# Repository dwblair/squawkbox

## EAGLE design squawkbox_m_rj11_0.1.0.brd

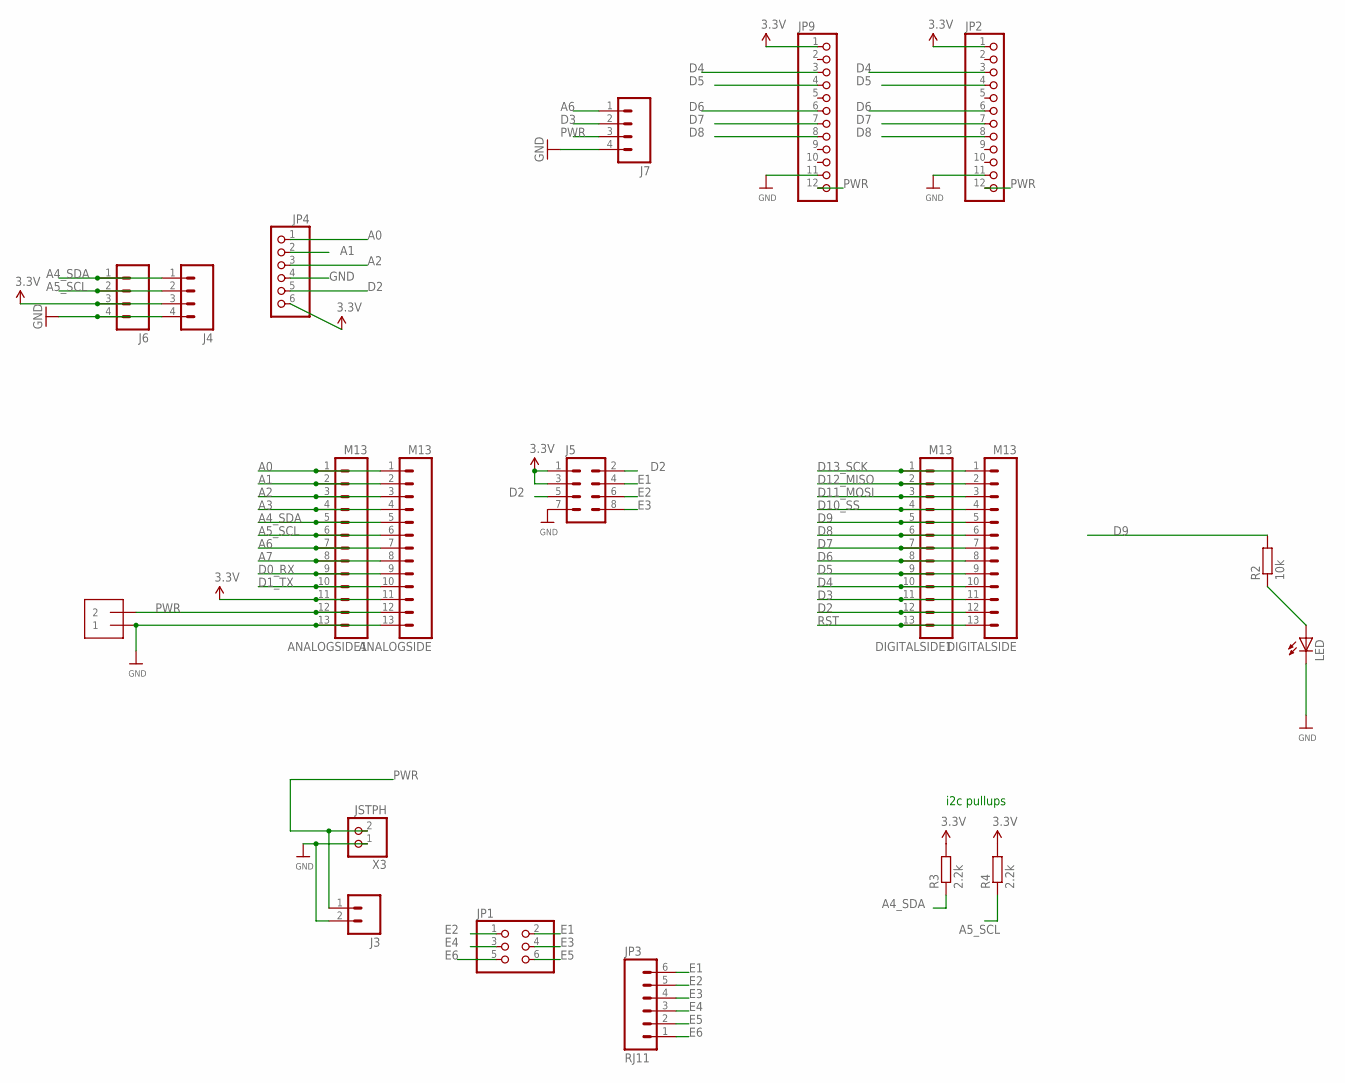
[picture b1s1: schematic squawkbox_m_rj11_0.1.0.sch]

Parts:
ANALOGSIDE, ANALOGSIDE1: M13; 1X13
DIGITALSIDE, DIGITALSIDE1: M13; 1X13
J2: 1X2-3.5MM
J3: M02PTH; 1X02
J4: M04PTH; 1X04
J5: M04X2; 2X4
J6, J7: M04SCREW; SCREWTERMINAL-3.5MM-4
JP1: PINHD-2X3; 2X03
JP2, JP9: PINHD-1X12-CB; 1X12-CB
JP3: RJ11; RJ11-6
JP4: PINHD-1X6-3.5MM; 1X06-3.5MM
LED: LED3MM
R2: 10k; 0204/7
R3, R4: 2.2k; 0204/7
X3: JSTPH; JSTPH2

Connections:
A0: ANALOGSIDE.1, ANALOGSIDE1.1, JP4.1
A1: ANALOGSIDE.2, ANALOGSIDE1.2, JP4.2
A2: ANALOGSIDE.3, ANALOGSIDE1.3, JP4.3
A3: ANALOGSIDE.4, ANALOGSIDE1.4
A4_SDA: ANALOGSIDE.5, ANALOGSIDE1.5, J4.1, J6.1, R3.1
A5_SCL: ANALOGSIDE.6, ANALOGSIDE1.6, J4.2, J6.2, R4.1
A6: ANALOGSIDE.7, ANALOGSIDE1.7, J7.1
A7: ANALOGSIDE.8, ANALOGSIDE1.8
D0_RX: ANALOGSIDE.9, ANALOGSIDE1.9
D1_TX: ANALOGSIDE.10, ANALOGSIDE1.10
D2: DIGITALSIDE.12, DIGITALSIDE1.12, J5.2, J5.5, JP4.5
D3: DIGITALSIDE.11, DIGITALSIDE1.11, J7.2
D4: DIGITALSIDE.10, DIGITALSIDE1.10, JP2.3, JP9.3
D5: DIGITALSIDE.9, DIGITALSIDE1.9, JP2.4, JP9.4
D6: DIGITALSIDE.8, DIGITALSIDE1.8, JP2.6, JP9.6
D7: DIGITALSIDE.7, DIGITALSIDE1.7, JP2.7, JP9.7
D8: DIGITALSIDE.6, DIGITALSIDE1.6, JP2.8, JP9.8
D9: DIGITALSIDE.5, DIGITALSIDE1.5, R2.2
D10_SS: DIGITALSIDE.4, DIGITALSIDE1.4
D11_MOSI: DIGITALSIDE.3, DIGITALSIDE1.3
D12_MISO: DIGITALSIDE.2, DIGITALSIDE1.2
D13_SCK: DIGITALSIDE.1, DIGITALSIDE1.1
E1: J5.4, JP1.2, JP3.6
E2: J5.6, JP1.1, JP3.5
E3: J5.8, JP1.4, JP3.4
E4: JP1.3, JP3.3
E5: JP1.6, JP3.2
E6: JP1.5, JP3.1
GND: ANALOGSIDE.13, ANALOGSIDE1.13, J2.1, J3.2, J4.4, J5.7, J6.4, J7.4, JP2.11, JP4.4, JP9.11, LED.K (C), X3.1
unnamed: LED.A, R2.1
PWR: ANALOGSIDE.12, ANALOGSIDE1.12, J2.2, J3.1, J7.3, JP2.12, JP9.12, X3.2
RST: DIGITALSIDE.13, DIGITALSIDE1.13
SPEAKER2+: JP2.10
SPEAKER2+1: JP9.10
VCC: ANALOGSIDE.11, ANALOGSIDE1.11, J4.3, J5.1, J5.3, J6.3, JP2.1, JP4.6, JP9.1, R3.2, R4.2

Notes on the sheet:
i2c pullups

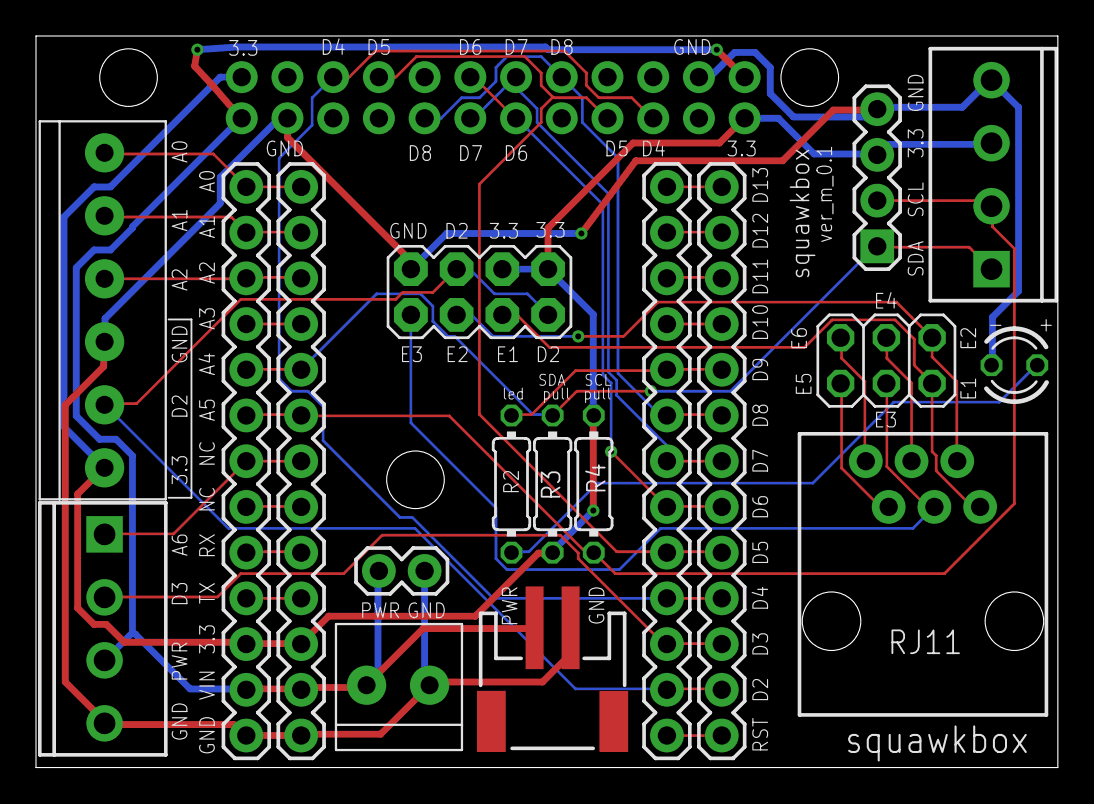
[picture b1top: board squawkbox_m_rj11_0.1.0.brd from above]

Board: 2 copper layers, 56.8 x 40.6 mm, 20 parts (0 on the bottom side), 33 nets.

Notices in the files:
parts and their libraries:
SparkFun-Connectors: Licensing: CC v3.0 Share-Alike You are welcome to use this library for commercial purposes.
microbuilder: This work is placed in the public domain, and may be freely used for commercial and non-commercial work with the following conditions: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
